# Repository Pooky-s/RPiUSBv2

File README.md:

# RPiUSBv2
This is a complete rework of the RPiUSB, an alternative to the Bash Bunny, based on a Raspberry Pi Zero (2w compatible). Ducky Script compatible and modular, the goal is to make the idea even better !

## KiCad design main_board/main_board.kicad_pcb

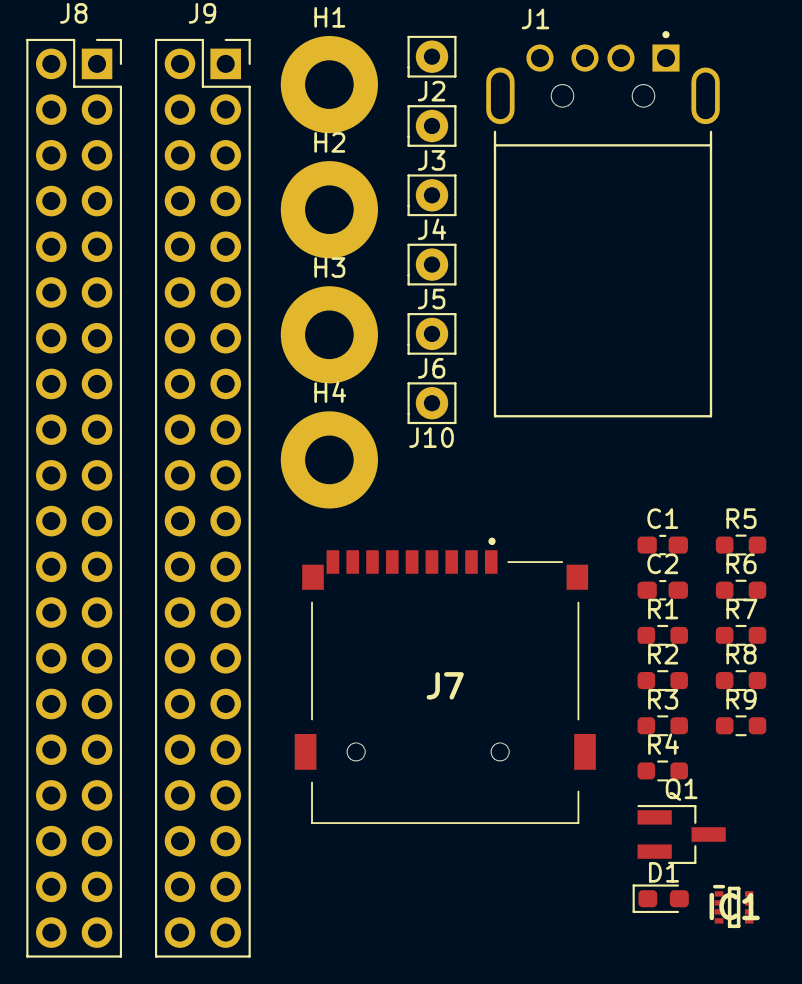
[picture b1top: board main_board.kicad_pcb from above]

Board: 2 copper layers, 28 parts (0 on the bottom side), 58 nets, no tracks yet.

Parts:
C1, C2: 1uf; C_0603_1608Metric_Pad1.08x0.95mm_HandSolder
D1: LED Status; LED_0603_1608Metric_Pad1.05x0.95mm_HandSolder
H1: MountingHole_Pads; MountingHole_2.7mm_M2.5_Pad
H2, H3, H4: MountingHole_Pad; MountingHole_2.7mm_M2.5_Pad
IC1: LM66200DRLR; SOTFL50P160X60-8N
J1: USB_A; MOLEX_48037-0001
J2, J3, J4, J10: Pogo pin; Pin_D0.9mm_L10.0mm_W2.4mm_FlatFork
J5: Pogo pin USB +; Pin_D0.9mm_L10.0mm_W2.4mm_FlatFork
J6: Pogo pin USB-; Pin_D0.9mm_L10.0mm_W2.4mm_FlatFork
J7: Micro_SD_Card; TF01A
J8, J9: Header RPi; PinSocket_2x20_P2.54mm_Vertical
Q1: 2N3904; SOT-23_Handsoldering
R1, R2: 1k5; R_0603_1608Metric_Pad0.98x0.95mm_HandSolder
R3, R4, R5, R6, R7, R8, R9: 33; R_0603_1608Metric_Pad0.98x0.95mm_HandSolder

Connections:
2: J8.2, J9.2
3: J8.3, J9.4
4: J8.4, J9.3
5: J8.5, J9.6
6: J8.6, J9.5
7: J8.7, J9.8
8: J8.8, J9.7
9: J8.9, J9.10
10: J8.10, J9.9
11: J8.11, J9.12
12: J8.12, J9.11
14: J8.14, J9.13
17: J8.17, J9.18
19: J8.19, J9.19
20: J8.20, J9.20
21: J8.21, J9.22
23: J8.23, J9.23
24: J8.24, J9.24
25: J8.25, J9.25
26: J8.26, J9.26
27: J8.27, J9.27
28: J8.28, J9.28
29: J8.29, J9.29
30: J8.30, J9.30
31: J8.31, J9.31
32: J8.32, J9.32
33: J8.33, J9.33
34: J8.34, J9.34
35: J8.35, J9.35
36: J8.36, J9.36
38: J8.38, J9.37
39: J8.39, J9.39
40: J8.40, J9.40
+3V3: J7.4 (VDD), R2.1
+5V: C1.1, J1.1 (VBUS), R9.1
+5VA: C2.2, J10.1
CMD: J8.16, R5.2
Clock: J8.15, R6.2
Data0: J8.18, R7.2
Data1: J8.22, R8.2
Data2: J8.37, R3.2
Data3: J8.13, R4.2
GND: D1.1 (K), H1.1, H2.1, H3.1, H4.1, IC1.1 (GND_1), IC1.5 (GND_2), J1.4 (GND), J4.1, J7.6 (VSS), Q1.2 (E)
LED STATUS: J2.1, R1.1
unnamed: D1.2 (A), Q1.3 (C), R2.2
unnamed: C1.2, IC1.3 (VIN1)
unnamed: C2.1, IC1.6 (VIN2)
unnamed: J7.5 (CLK), R6.1
unnamed: J7.3 (CMD), R5.1
unnamed: J7.7 (DAT0), R7.1
unnamed: J7.8 (DAT1), R8.1
unnamed: J7.1 (DAT2), R3.1
unnamed: J7.2 (DAT3/CD), R4.1
unnamed: Q1.1 (B), R1.2
USB+: J1.3 (D+), J6.1
USB-: J1.2 (D-), J5.1
VCC: IC1.2 (VOUT_1), IC1.7 (VOUT_2), J3.1
VIN_STATUS: IC1.8 (ST), R9.2
